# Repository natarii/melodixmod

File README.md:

MelodixMod
========
The MelodixMod project adds internal memory to the TOA MELODIX ML-304 melody generator. This repository also contains WIP hardware and software documentation for the original device.

## Overview
ML-304 devices use a Yamaha YM2203 OPN FM sound source to play back melodies, chimes and tones stored on memory cards. The MelodixMod system serves as an effective replacement for these cards. Full function of the original unit is retained -- physical cards inserted into the slots will override any data stored on MelodixMod's flash. A bank switching option is available through a hole on the rear panel which allows the user to switch between multiple banks of simulated cards. Impact to the device's appearance is also minimized, with the only change visible from the outside being the removal of a grounding screw.

### Mod Files
- `Logic` - Data to program the mod's decode logic chip
- `MCU` - Program for the mod's ATTiny85 MCU
- `PCB` - EAGLE schematic and PCB design files
- `PCBSpacer` - OpenSCAD design file and STL for a 3D-printable spacer to support the mod PCB

### Research Files
- `Disassembly` - Original ML-304 program disassembly
- `FujisokuBProgrammer` Arduino Mega-based programmer for Melodix cards
- `MelodixCard` - Information about the data format on Melodix cards

## MELODIX CARD information

The memory cards used in the ML-304 are pre-programmed and follow the Fujisoku B-series physical and electrical standard. Despite a very vague resemblance to PCMCIA and other common memory cards, this is an obsolete and relatively rare format. As the Melodix units are niche in addition to not having been marketed outside of Japan, original TOA cards fetch prices in the hundreds of USD range on auction sites, making it infeasible for most (certainly me!) to collect any more than the less-desirable cards.

## Why making reproduction cards isn't viable

Fujisoku B-series cards use very thin contacts on the card side, which mate with "forks" in the slot. A reproduction card could likely be made out of very thin PCB, but there is not much remaining height for components on the board. Surface mount parts may be viable (assuming a programmer which the cards could slot into existed -- more on that later), but any through-hole parts like socketed memory would not be usable without hanging further than usual out of the front of the device (outside of the normal card form factor).

UV EPROM, EEPROM, flash, and SRAM-based B-series cards were produced, but these are also becoming increasingly difficult to find. As these cards are writable, they also require hardware modifications to the Melodix unit as it does not drive all of the control lines they need.

## Card slot availability

In 2021, the availability of B-series card slots was essentially nil. An exhaustive personal and crowdsourced search turned up no supplies of slots, aside from ones that could be removed from an existing piece of equipment. I was also not able to establish an actual part number or manufacturer for the slots.

In 2023, some slots have turned up on US eBay. I also found further documentation which reveals some card slot part numbers, which are listed below. Note that not all of these are usable as replacements in the original device, but could be used in an external programmer or dumping tool.

- ITT Cannon 990-2000-053 (right angle pins)
- ITT Cannon DICMI-38S-RPC-01 (right angle pins)
- Hakuto BC1R (right angle pins)
- Hakuto BC1S (straight pins)

Regardless of any current availability of card slots, they are no longer being produced and supplies will eventually run out. This is another nail in the coffin for using the programmable variants as reproduction cards.

## I made a reproduction card anyway

Before deciding to proceed with an internal card modification, I ended up purchasing an SRAM card and designing an Arduino Mega-based programmer for it. The programmer can connect to the Mega board with no extra components needed, and the code allows for card memory to be uploaded and downloaded via XMODEM. I also performed the required modifications to the Melodix PCB to allow SRAM cards to be used.

It is also possible to adapt these cards to be used in a standard EPROM programmer.

## Related WIP projects / TODO

  * Verify v1.1 mod PCB
  * Disassembly of ML-304/ML-301 MCU program (nearly complete, needs some updates now that I have the hardware to reference, also needs to be done in proper f9dasm format rather than simple text find-and-replace)
  * MAME driver for Melodix series (working, needs better integration with MAME cartridge system, needs UI)
  * Melodix card to VGM conversion utility (working, needs cleanup but otherwise complete)
  * MIDI to Melodix card conversion utility (partially working)
  * Replacement main MCU (not started)
  * Document the process to prepare data for MelodixMod's flash (really just concatenate 32KByte binaries)

## Acknowledgements
  * Thanks to Hind for providing the initial MCU ROM dump.

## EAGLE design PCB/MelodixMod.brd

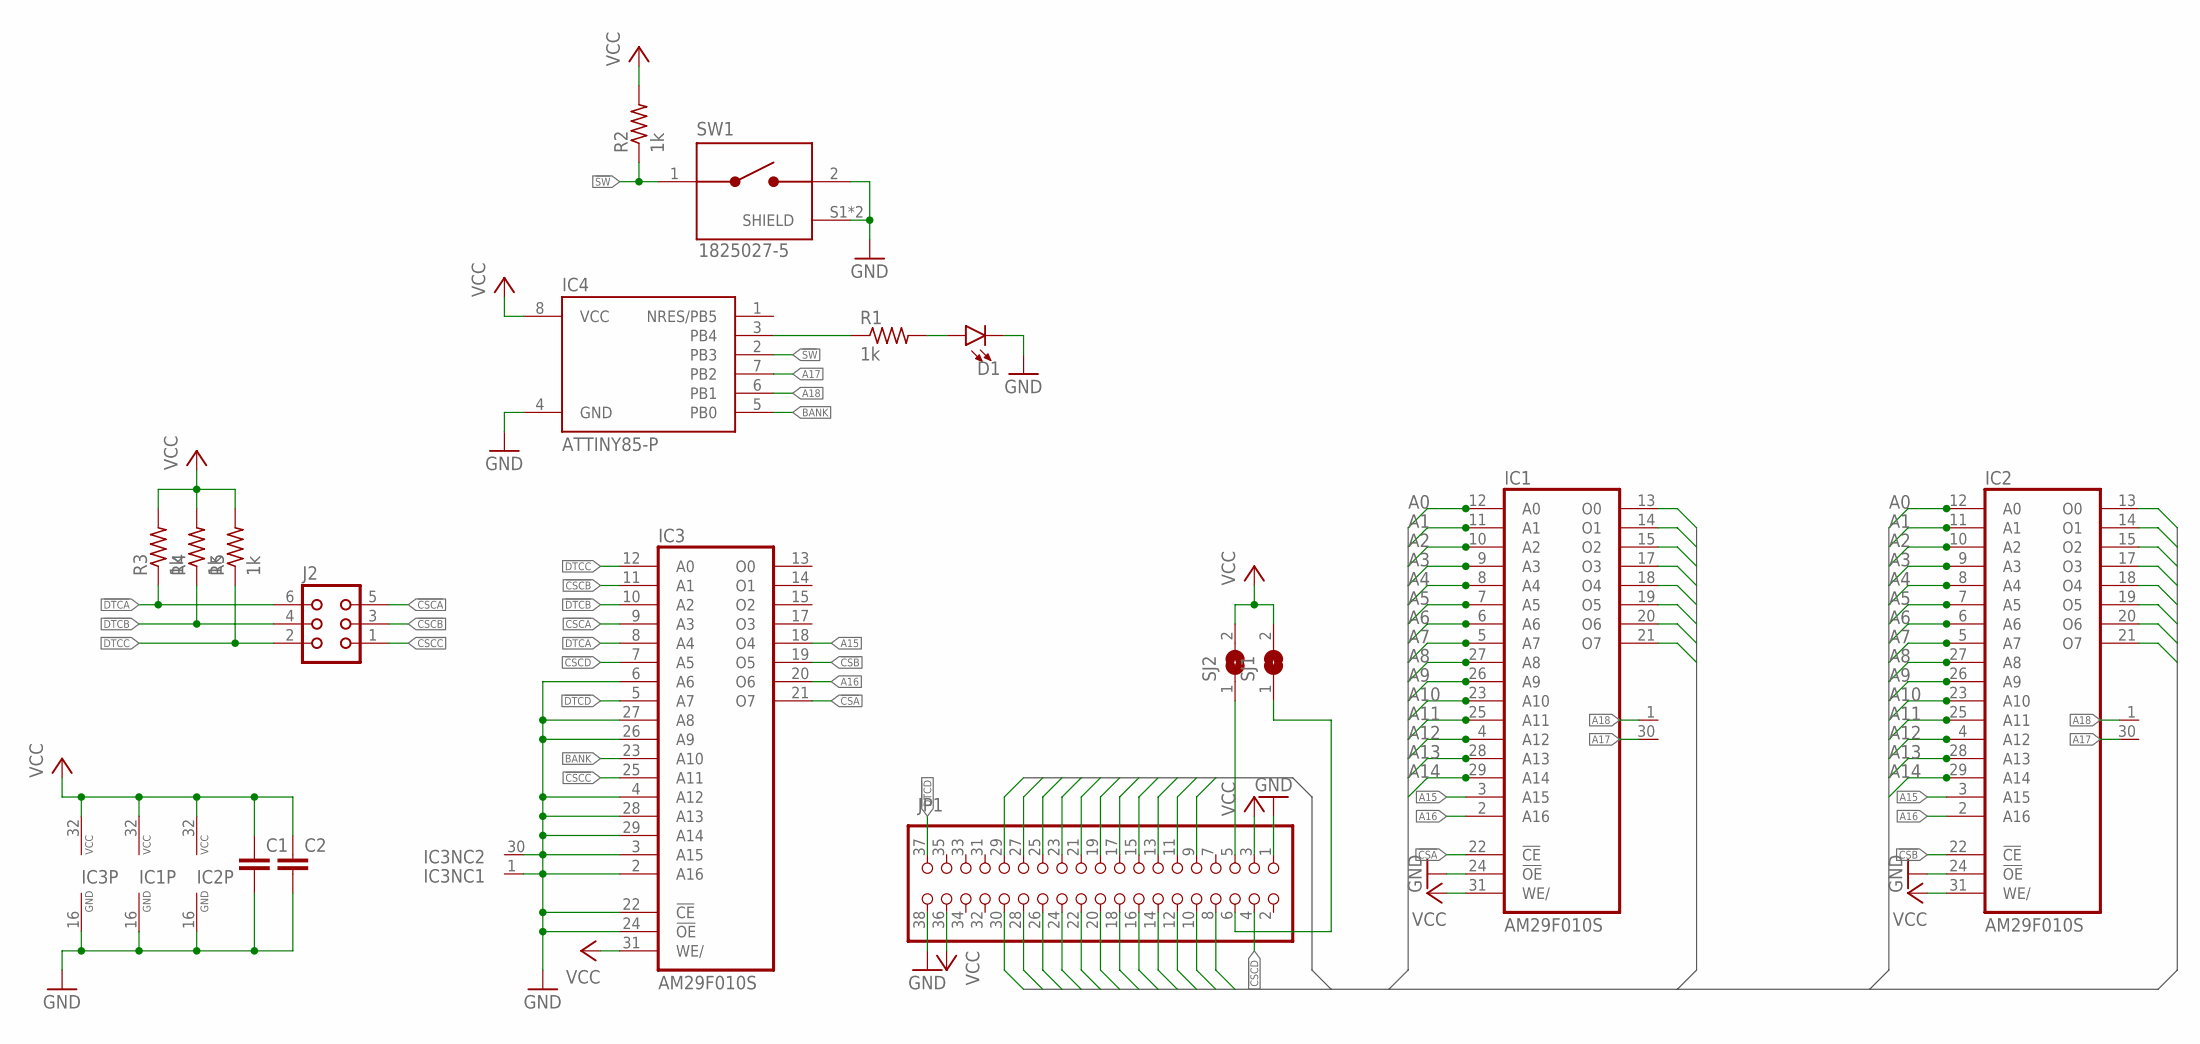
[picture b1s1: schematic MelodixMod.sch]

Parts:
C1, C2: C-EU025-024X044; C025-024X044
D1: LED5MM; LED_5MM
IC1, IC2, IC3: AM29F010S; PLCC-SR32
IC4: ATTINY85-P; PDIP08_300MIL
J2: CON06
JP1: FUJISOKU_B_SLOT; FUJISOKU_B_FP
R1, R2, R3, R4, R5: 1k; 0204/7
SJ1, SJ2: SJ
SW1: 1825027-5; SW_1825027-5

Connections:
!CSA: IC1.22 (!CE), IC3.21 (O7)
!CSB: IC2.22 (!CE), IC3.19 (O5)
!CSCA: IC3.9 (A3), J2.5
!CSCB: IC3.11 (A1), J2.3
!CSCC: IC3.25 (A11), J2.1
!CSCD: IC3.7 (A5), JP1.4 (!CE1)
!DTCA: IC3.8 (A4), J2.6, R3.1
!DTCB: IC3.10 (A2), J2.4, R4.1
!DTCC: IC3.12 (A0), J2.2, R5.1
!DTCD: IC3.5 (A7), JP1.37 (!CARD_DET)
!SW: IC4.2 (PB3), R2.1, SW1.1
A0: IC1.12 (A0), IC2.12 (A0), JP1.16 (A0)
A1: IC1.11 (A1), IC2.11 (A1), JP1.17 (A1)
A2: IC1.10 (A2), IC2.10 (A2), JP1.18 (A2)
A3: IC1.9 (A3), IC2.9 (A3), JP1.19 (A3)
A4: IC1.8 (A4), IC2.8 (A4), JP1.20 (A4)
A5: IC1.7 (A5), IC2.7 (A5), JP1.21 (A5)
A6: IC1.6 (A6), IC2.6 (A6), JP1.22 (A6)
A7: IC1.5 (A7), IC2.5 (A7), JP1.23 (A7)
A8: IC1.27 (A8), IC2.27 (A8), JP1.24 (A8)
A9: IC1.26 (A9), IC2.26 (A9), JP1.25 (A9)
A10: IC1.23 (A10), IC2.23 (A10), JP1.26 (A10)
A11: IC1.25 (A11), IC2.25 (A11), JP1.27 (A11)
A12: IC1.4 (A12), IC2.4 (A12), JP1.28 (A12)
A13: IC1.28 (A13), IC2.28 (A13), JP1.29 (A13)
A14: IC1.29 (A14), IC2.29 (A14), JP1.30 (A14)
A15: IC1.3 (A15), IC2.3 (A15), IC3.18 (O4)
A16: IC1.2 (A16), IC2.2 (A16), IC3.20 (O6)
A17: IC1.30 (NC), IC2.30 (NC), IC4.7 (PB2)
A18: IC1.1 (NC), IC2.1 (NC), IC4.6 (PB1)
BANK: IC3.23 (A10), IC4.5 (PB0)
D0: IC1.13 (O0), IC2.13 (O0), JP1.8 (D0)
D1: IC1.14 (O1), IC2.14 (O1), JP1.9 (D1)
D2: IC1.15 (O2), IC2.15 (O2), JP1.10 (D2)
D3: IC1.17 (O3), IC2.17 (O3), JP1.11 (D3)
D4: IC1.18 (O4), IC2.18 (O4), JP1.12 (D4)
D5: IC1.19 (O5), IC2.19 (O5), JP1.13 (D5)
D6: IC1.20 (O6), IC2.20 (O6), JP1.14 (D6)
D7: IC1.21 (O7), IC2.21 (O7), JP1.15 (D7)
GND: C1.2, C2.2, D1.K (C), IC1.16 (GND), IC1.24 (!OE), IC2.16 (GND), IC2.24 (!OE), IC3.1 (NC), IC3.2 (A16), IC3.3 (A15), IC3.4 (A12), IC3.6 (A6), IC3.16 (GND), IC3.22 (!CE), IC3.24 (!OE), IC3.26 (A9), IC3.27 (A8), IC3.28 (A13), IC3.29 (A14), IC3.30 (NC), IC4.4 (GND), JP1.1 (GND), JP1.38 (GND), SW1.2, SW1.S1 (SHIELD), SW1.S2 (SHIELD)
unnamed: IC4.3 (PB4), R1.1
unnamed: D1.A, R1.2
unnamed: JP1.5 (CE2), SJ2.1
unnamed: JP1.6 (!WE), SJ1.1
VCC: C1.1, C2.1, IC1.31 (WE/), IC1.32 (VCC), IC2.31 (WE/), IC2.32 (VCC), IC3.31 (WE/), IC3.32 (VCC), IC4.8 (VCC), JP1.3 (VCC), JP1.36 (VCC), R2.2, R3.2, R4.2, R5.2, SJ1.2, SJ2.2

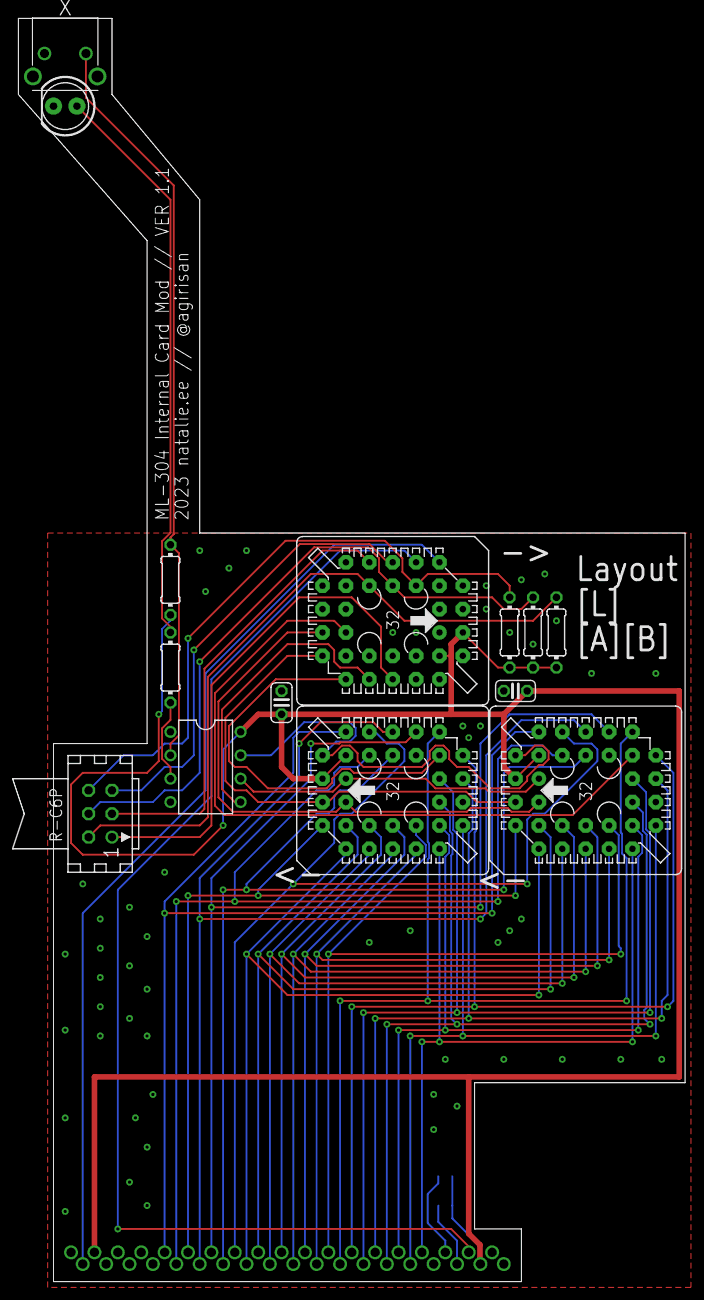
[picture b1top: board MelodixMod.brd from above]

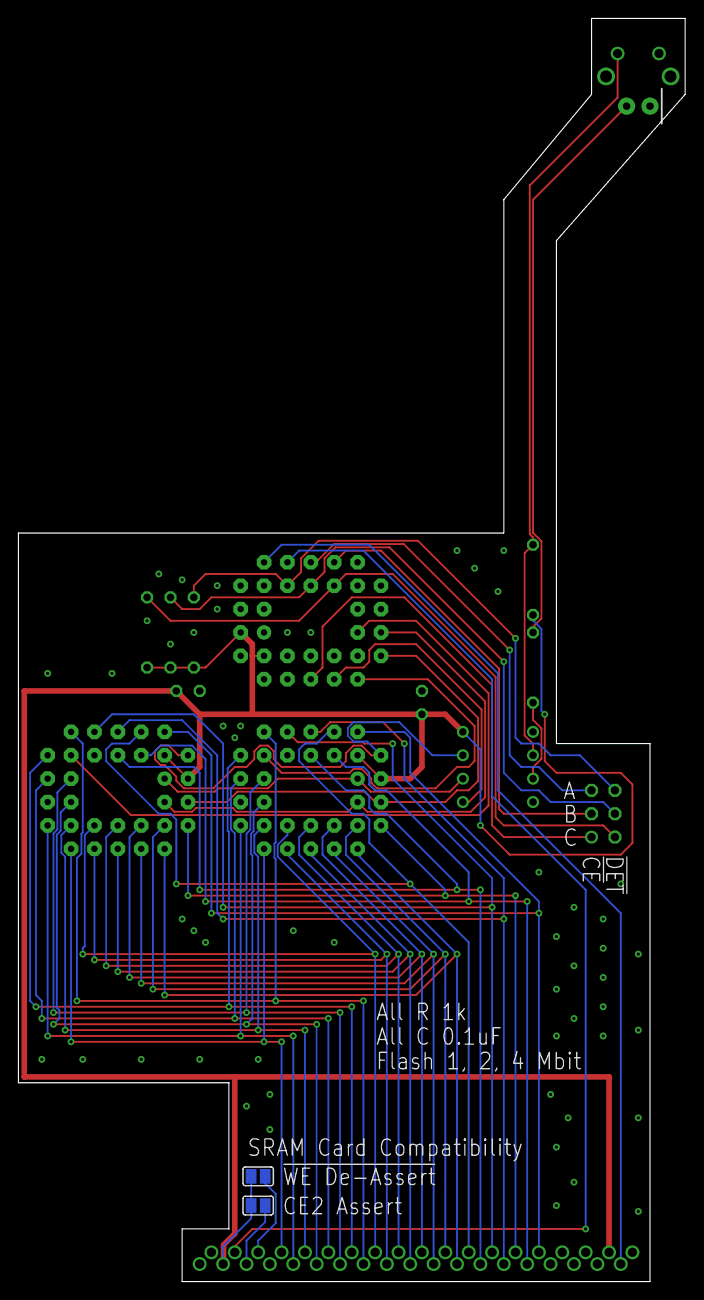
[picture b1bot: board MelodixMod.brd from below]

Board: 2 copper layers, 72.4 x 137.2 mm, 17 parts (2 on the bottom side), 45 nets.

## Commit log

2022-04-16 Initial commit (MCU)
2022-04-16 Add chip select/bank switching logic
2022-04-16 Add readme
2022-04-16 Add WIP MCU disassembly
2023-11-05 Readme updates
2023-11-05 Add card programmer
2023-11-07 Add v1.1 PCB
2023-11-07 Add PCB spacer 3D design files
2024-01-07 Improve names of note setup routines
2024-01-07 Update MCU disassembly
2024-06-26 Add card data format information
2024-06-29 Start using f9dasm properly, deprecate old text find-and-replace disassembly
2024-06-29 Update disassembly readme
2024-06-29 Disassembly: Fix typo
2024-06-29 Add pictures
2024-07-03 Update disassembly
2024-07-05 Disassembly: fix hardware info
2024-07-09 Disassembly: Fix typo'd address for comment
2024-07-10 Disassembly: Set labels for MCU internal IO and peripherals
2024-07-10 Disassembly: Correct constants on LDX instructions
2024-07-10 Update disassembly, card data format
2024-10-17 Disassembly: clarify a few ML-301 specifics
2024-10-17 Disassembly: clarify ML-301 westminster behavior

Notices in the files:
parts and their libraries:
SparkFun-LED: Licensing: Creative Commons ShareAlike 4.0 International - https://creativecommons.org/licenses/by-sa/4.0
